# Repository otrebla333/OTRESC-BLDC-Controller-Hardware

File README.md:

# OTRESC-BLDC-Controller-Hardware

OTRESC-BLDC-Controller

A Brushless DC motor controller with position and speed control.

    Uses a SAMC21 microcontroller.
    Uses the DRV83XX gate driver.
    Uses the TLV493D magnetic sensor to read the shaft position and speed.

Follow the project here: https://hackaday.io/project/90283-llm-bldc-controller

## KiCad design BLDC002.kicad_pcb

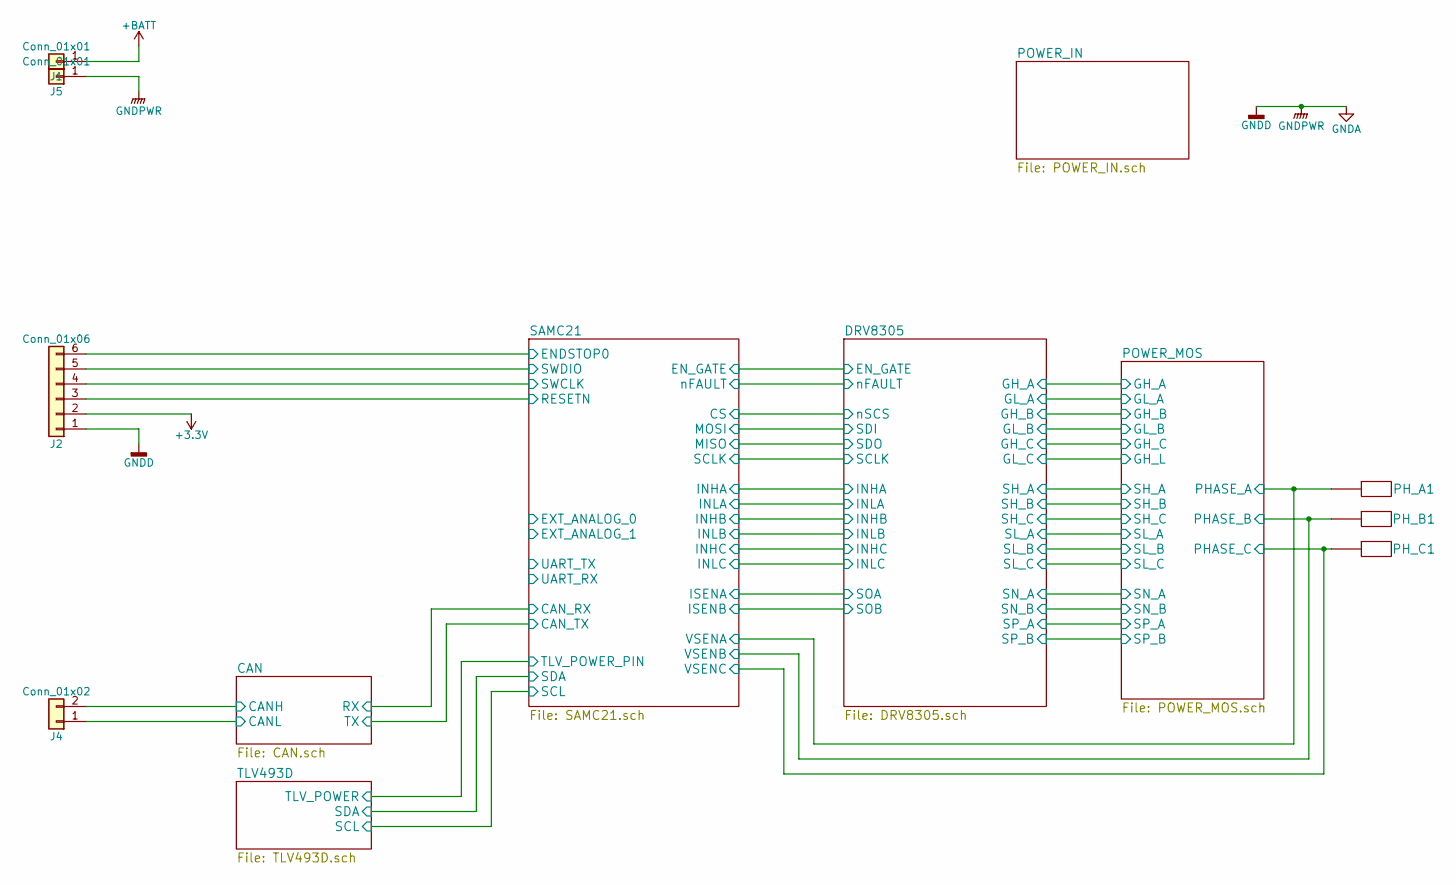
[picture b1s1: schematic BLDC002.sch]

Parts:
J1, J5: Conn_01x01; POWER_PAD_TH
J2: Conn_01x06; 6_pin_1.25mm_vias
J4: Conn_01x02; MC34641
PH_A1: POWER_PAD; POWER_PAD_PHASE_MIX_5x4
PH_B1: POWER_PAD; POWER_PAD_PHASE_MIX_5x4
PH_C1: POWER_PAD; POWER_PAD_PHASE_MIX_5x4

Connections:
+3V3: J2.2; also elsewhere on the board
+BATT: J1.1; also elsewhere on the board
/CAN/CANH: J4.2; also elsewhere on the board
/CAN/CANL: J4.1; also elsewhere on the board
/SAMC21/ENDSTOP0: J2.6; also elsewhere on the board
/SAMC21/RESETN: J2.3; also elsewhere on the board
/SAMC21/SWCLK: J2.4; also elsewhere on the board
/SAMC21/SWDIO: J2.5; also elsewhere on the board
GNDA: J2.1, J5.1; also elsewhere on the board

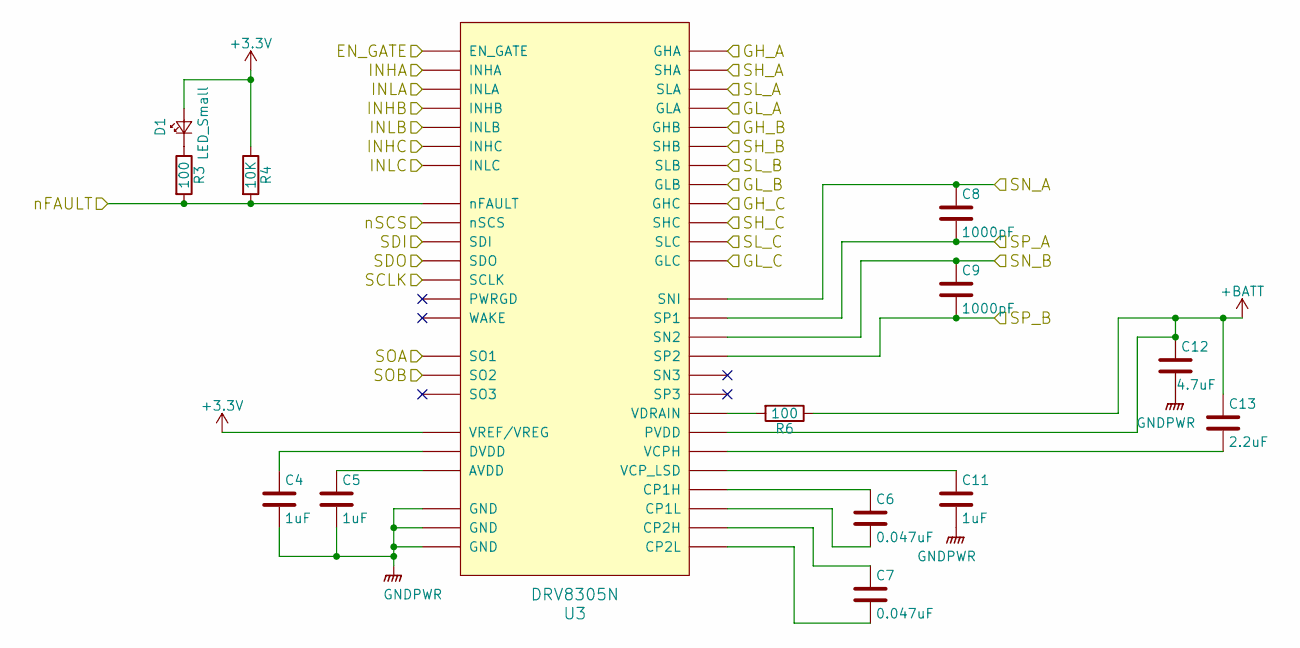
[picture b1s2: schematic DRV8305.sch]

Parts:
C4, C5, C11: 1uF; C_0603_HandSoldering
C6, C7: 0.047uF; C_0603_HandSoldering
C8, C9: 1000pF; C_0603_HandSoldering
C12: 4.7uF; C_0603_HandSoldering
C13: 2.2uF; C_0603_HandSoldering
D1: LED_Small; LED_0805_HandSoldering
R3, R6: 100; R_0603_HandSoldering
R4: 10K; R_0603_HandSoldering
U3: DRV8305N; QFP50P900X900X120-49N

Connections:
+3V3: D1.2 (A), R4.1, U3.48 (VREF/VREG); also elsewhere on the board
+BATT: C12.1, C13.1, R6.1, U3.41 (PVDD); also elsewhere on the board
/DRV8305/EN_GATE: U3.1 (EN_GATE); also elsewhere on the board
/DRV8305/GH_A: U3.36 (GHA); also elsewhere on the board
/DRV8305/GH_B: U3.29 (GHB); also elsewhere on the board
/DRV8305/GH_C: U3.28 (GHC); also elsewhere on the board
/DRV8305/GL_A: U3.33 (GLA); also elsewhere on the board
/DRV8305/GL_B: U3.32 (GLB); also elsewhere on the board
/DRV8305/INHA: U3.2 (INHA); also elsewhere on the board
/DRV8305/INHB: U3.4 (INHB); also elsewhere on the board
/DRV8305/INHC: U3.6 (INHC); also elsewhere on the board
/DRV8305/INLA: U3.3 (INLA); also elsewhere on the board
/DRV8305/INLB: U3.5 (INLB); also elsewhere on the board
/DRV8305/INLC: U3.7 (INLC); also elsewhere on the board
/DRV8305/SCLK: U3.12 (SCLK); also elsewhere on the board
/DRV8305/SL_A: C8.1, U3.23 (SNI), U3.34 (SLA); also elsewhere on the board
/DRV8305/SL_B: C9.1, U3.21 (SN2), U3.31 (SLB); also elsewhere on the board
/DRV8305/nFAULT: R3.2, R4.2, U3.8 (nFAULT); also elsewhere on the board
/POWER_MOS/GH_L: U3.25 (GLC); also elsewhere on the board
/POWER_MOS/PHASE_A: U3.35 (SHA); also elsewhere on the board
/POWER_MOS/PHASE_B: U3.30 (SHB); also elsewhere on the board
/POWER_MOS/PHASE_C: U3.27 (SHC); also elsewhere on the board
/SAMC21/CS: U3.9 (nSCS); also elsewhere on the board
/SAMC21/ISENA: U3.16 (SO1); also elsewhere on the board
/SAMC21/ISENB: U3.17 (SO2); also elsewhere on the board
/SAMC21/MISO: U3.11 (SDO); also elsewhere on the board
/SAMC21/MOSI: U3.10 (SDI); also elsewhere on the board
GNDA: C4.2, C5.2, C8.2, C9.2, C11.2, C12.2, U3.14 (GND), U3.22 (SP2), U3.24 (SP1), U3.26 (SLC), U3.45 (GND), U3.49 (GND); also elsewhere on the board
unnamed: C4.1, U3.46 (DVDD)
unnamed: C5.1, U3.15 (AVDD)
unnamed: C6.1, U3.43 (CP1H)
unnamed: C6.2, U3.42 (CP1L)
unnamed: C7.1, U3.39 (CP2H)
unnamed: C7.2, U3.40 (CP2L)
unnamed: C11.1, U3.37 (VCP_LSD)
unnamed: C13.2, U3.38 (VCPH)
unnamed: D1.1 (K), R3.1
unnamed: R6.2, U3.44 (VDRAIN)

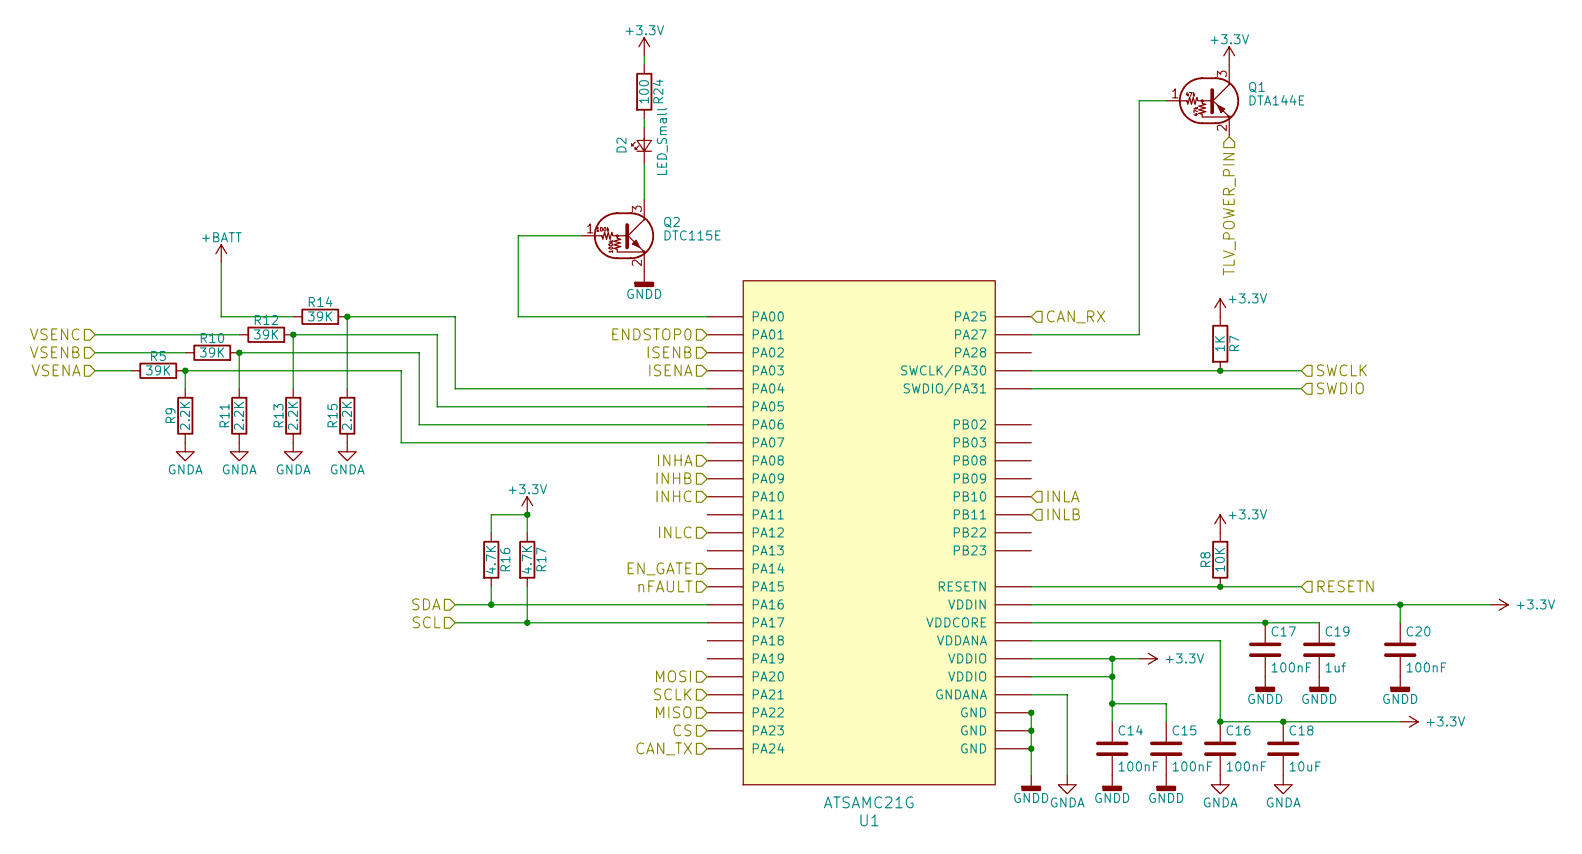
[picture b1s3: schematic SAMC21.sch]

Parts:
C14, C15, C16, C17, C20: 100nF; C_0603_HandSoldering
C18: 10uF; C_0603_HandSoldering
C19: 1uf; C_0603_HandSoldering
D2: LED_Small; LED_0805_HandSoldering
Q1: DTA144E; SC75
Q2: DTC115E; SC75
R5, R10, R12, R14: 39K; R_0603_HandSoldering
R7: 1K; R_0603_HandSoldering
R8: 10K; R_0603_HandSoldering
R9, R11, R13, R15: 2.2K; R_0603_HandSoldering
R16, R17: 4.7K; R_0603_HandSoldering
R24: 100; R_0603_HandSoldering
U1: ATSAMC21G; QFP50P900X900X120-48N

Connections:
+3V3: C14.1, C15.1, C16.1, C18.1, C20.1, Q1.3 (C), R7.1, R8.2, R16.1, R17.1, R24.1, U1.6 (VDDANA), U1.17 (VDDIO), U1.36 (VDDIO), U1.44 (VDDIN); also elsewhere on the board
+BATT: R14.1; also elsewhere on the board
/DRV8305/EN_GATE: U1.23 (PA14); also elsewhere on the board
/DRV8305/INHA: U1.13 (PA08); also elsewhere on the board
/DRV8305/INHB: U1.14 (PA09); also elsewhere on the board
/DRV8305/INHC: U1.15 (PA10); also elsewhere on the board
/DRV8305/INLA: U1.19 (PB10); also elsewhere on the board
/DRV8305/INLB: U1.20 (PB11); also elsewhere on the board
/DRV8305/INLC: U1.21 (PA12); also elsewhere on the board
/DRV8305/SCLK: U1.30 (PA21); also elsewhere on the board
/DRV8305/nFAULT: U1.24 (PA15); also elsewhere on the board
/POWER_MOS/PHASE_A: R5.1; also elsewhere on the board
/POWER_MOS/PHASE_B: R10.1; also elsewhere on the board
/POWER_MOS/PHASE_C: R12.1; also elsewhere on the board
/SAMC21/CAN_RX: U1.34 (PA25); also elsewhere on the board
/SAMC21/CAN_TX: U1.33 (PA24); also elsewhere on the board
/SAMC21/CS: U1.32 (PA23); also elsewhere on the board
/SAMC21/ENDSTOP0: U1.2 (PA01); also elsewhere on the board
/SAMC21/ISENA: U1.4 (PA03); also elsewhere on the board
/SAMC21/ISENB: U1.3 (PA02); also elsewhere on the board
/SAMC21/MISO: U1.31 (PA22); also elsewhere on the board
/SAMC21/MOSI: U1.29 (PA20); also elsewhere on the board
/SAMC21/RESETN: R8.1, U1.40 (RESETN); also elsewhere on the board
/SAMC21/SCL: R17.2, U1.26 (PA17); also elsewhere on the board
/SAMC21/SDA: R16.2, U1.25 (PA16); also elsewhere on the board
/SAMC21/SWCLK: R7.2, U1.45 (SWCLK/PA30); also elsewhere on the board
/SAMC21/SWDIO: U1.46 (SWDIO/PA31); also elsewhere on the board
/TLV493D/TLV_POWER: Q1.2 (E); also elsewhere on the board
GNDA: C14.2, C15.2, C16.2, C17.2, C18.2, C19.2, C20.2, Q2.2 (E), R9.1, R11.1, R13.1, R15.1, U1.5 (GNDANA), U1.18 (GND), U1.35 (GND), U1.42 (GND); also elsewhere on the board
unnamed: C17.1, C19.1, U1.43 (VDDCORE)
unnamed: D2.1 (K), Q2.3 (C)
unnamed: D2.2 (A), R24.2
unnamed: Q1.1 (B), U1.39 (PA27)
unnamed: Q2.1 (B), U1.1 (PA00)
unnamed: R5.2, R9.2, U1.12 (PA07)
unnamed: R10.2, R11.2, U1.11 (PA06)
unnamed: R12.2, R13.2, U1.10 (PA05)
unnamed: R14.2, R15.2, U1.9 (PA04)

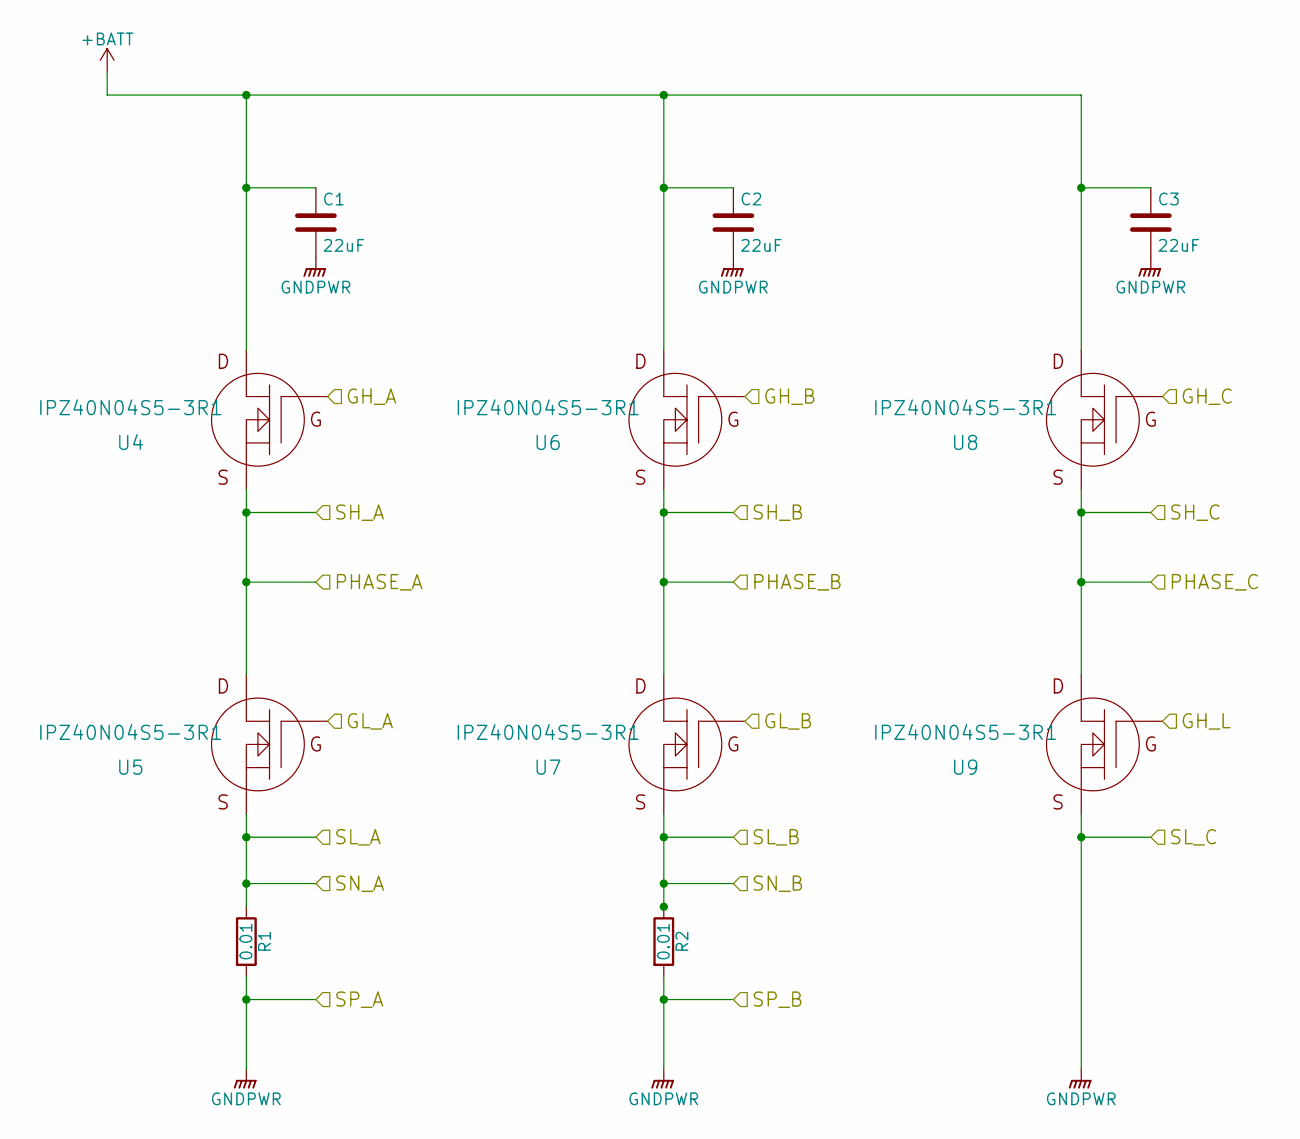
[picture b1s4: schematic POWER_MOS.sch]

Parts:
C1, C2, C3: 22uF; C_0603_HandSoldering
R1, R2: 0.01; R_1210
U4, U5, U6, U7, U8, U9: IPZ40N04S5-3R1; TSDSON_TH

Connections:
+BATT: C1.1, C2.1, C3.1, U4.5 (D), U6.5 (D), U8.5 (D); also elsewhere on the board
/DRV8305/GH_A: U4.4 (G); also elsewhere on the board
/DRV8305/GH_B: U6.4 (G); also elsewhere on the board
/DRV8305/GH_C: U8.4 (G); also elsewhere on the board
/DRV8305/GL_A: U5.4 (G); also elsewhere on the board
/DRV8305/GL_B: U7.4 (G); also elsewhere on the board
/DRV8305/SL_A: R1.1, U5.1 (S); also elsewhere on the board
/DRV8305/SL_B: R2.1, U7.1 (S); also elsewhere on the board
/POWER_MOS/GH_L: U9.4 (G); also elsewhere on the board
/POWER_MOS/PHASE_A: U4.1 (S), U5.5 (D); also elsewhere on the board
/POWER_MOS/PHASE_B: U6.1 (S), U7.5 (D); also elsewhere on the board
/POWER_MOS/PHASE_C: U8.1 (S), U9.5 (D); also elsewhere on the board
GNDA: C1.2, C2.2, C3.2, R1.2, R2.2, U9.1 (S); also elsewhere on the board

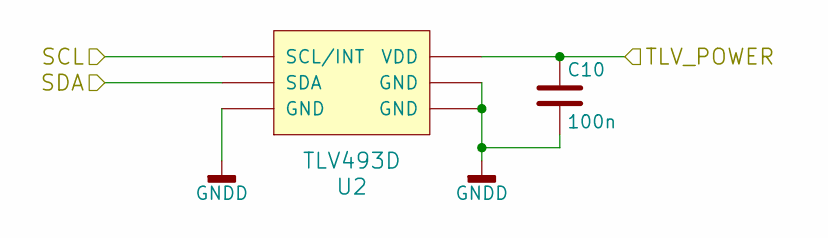
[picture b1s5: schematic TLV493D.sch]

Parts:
C10: 100n; C_0603_HandSoldering
U2: TLV493D; TSOP-6

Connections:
/SAMC21/SCL: U2.1 (SCL/INT); also elsewhere on the board
/SAMC21/SDA: U2.6 (SDA); also elsewhere on the board
/TLV493D/TLV_POWER: C10.1, U2.4 (VDD); also elsewhere on the board
GNDA: C10.2, U2.2 (GND), U2.3 (GND), U2.5 (GND); also elsewhere on the board

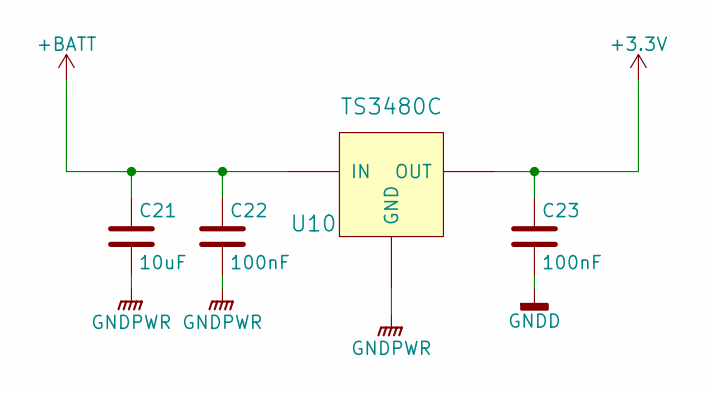
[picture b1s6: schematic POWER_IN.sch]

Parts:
C21: 10uF; C_0603_HandSoldering
C22, C23: 100nF; C_0603_HandSoldering
U10: TS3480C; SOT-23

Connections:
+3V3: C23.1, U10.1 (OUT); also elsewhere on the board
+BATT: C21.1, C22.1, U10.2 (IN); also elsewhere on the board
GNDA: C21.2, C22.2, C23.2, U10.3 (GND); also elsewhere on the board

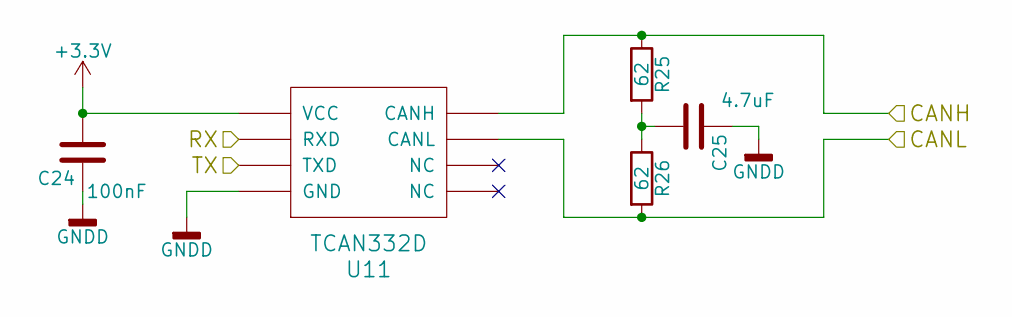
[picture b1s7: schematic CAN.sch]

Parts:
C24: 100nF; C_0603_HandSoldering
C25: 4.7uF; C_0603_HandSoldering
R25, R26: 62; R_0603_HandSoldering
U11: TCAN332D; SOT-23-8

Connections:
+3V3: C24.2, U11.3 (VCC); also elsewhere on the board
/CAN/CANH: R25.1, U11.7 (CANH); also elsewhere on the board
/CAN/CANL: R26.2, U11.6 (CANL); also elsewhere on the board
/SAMC21/CAN_RX: U11.4 (RXD); also elsewhere on the board
/SAMC21/CAN_TX: U11.1 (TXD); also elsewhere on the board
GNDA: C24.1, C25.1, U11.2 (GND); also elsewhere on the board
unnamed: C25.2, R25.2, R26.1

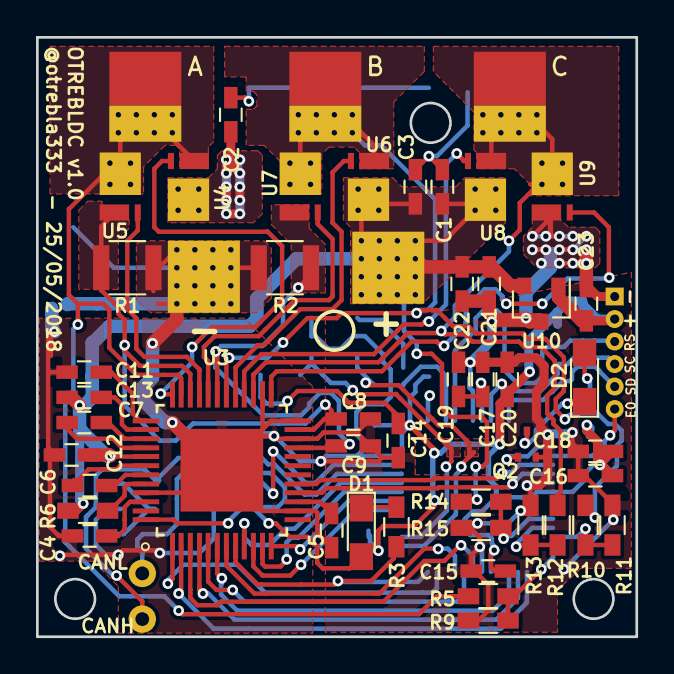
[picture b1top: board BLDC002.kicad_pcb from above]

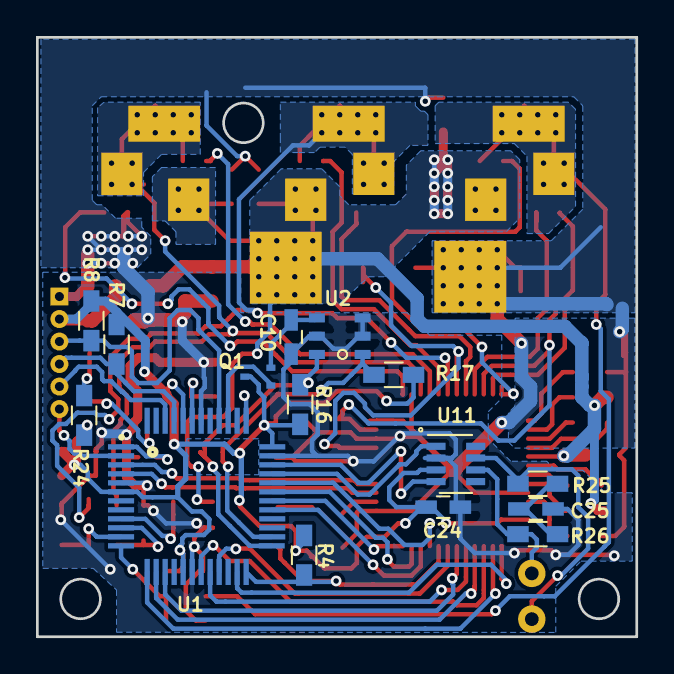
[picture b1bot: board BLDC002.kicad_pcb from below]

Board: 2 copper layers, 33.3 x 33.3 mm, 67 parts (16 on the bottom side), 59 nets.

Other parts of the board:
A: POWER_PAD; POWER_PAD_PHASE_MIX_5x4
B: POWER_PAD; POWER_PAD_PHASE_MIX_5x4
C: POWER_PAD; POWER_PAD_PHASE_MIX_5x4

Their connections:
/POWER_MOS/PHASE_A: A.1; also elsewhere on the board
/POWER_MOS/PHASE_B: B.1; also elsewhere on the board
/POWER_MOS/PHASE_C: C.1; also elsewhere on the board

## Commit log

2018-06-11 Create LICENSE
